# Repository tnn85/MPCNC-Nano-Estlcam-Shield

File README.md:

**<<<BITTE BEACHTEN: Die Platine darf ausdrücklich NUR für die private Verwendung hergestellt werden. Der Weiterverkauf sowohl gewerblich als auch privat (darunter fällt auch der der Verkauf als "gebraucht") ist nicht gestattet. D.h. bitte nicht aus ökonomischen Gründen mehrere Platinen bestellen und dann die übrigen Platinen auf Ebay/Ebay Kleinanzeigen/Amazon/Facebook oder anderen Handelsplattformen öffentlich/halböffentlich anbieten! Beachtet die Lizenzbedingungen am Ende dises Dokuments. Danke für dein/euer Verständnis.>>>**  

Falls Interesse an der Platine besteht und ihr diese nicht selbst fertigen (ätzen/fräsen) wollt oder könnt, bietet der Moderator der FB-Gruppe "Uncle Phil's Werkstatt" die Bausätze an. Ich habe **nur** ihm gestattet, die Platine anzubieten. Andere Bezugsquellen sind von mir nicht genehmigt.

# MPCNC-Nano-Estlcam-Shield
English: A CNC shield for the MPCNC in conjunction with Estlcam  
Deutsch: Ein CNC Shield für die MPCNC in Verbindung mit Estlcam

# Konzept:  
Das MPCNC Nano Esltcam Shield stellt eine CNC Steuerungssplatine für die MPCNC bereit, die Einsteigern eine kostengünstige, auf die CNC-Maschine (MPCNC) und Software (Estlcam) zugeschnittene Steuerung als Schnittstellenlösung zwischen Maschine und Estlcam anbietet.  Die Steuerung bietet mehr Funktionalität als vergleichbare Steuerungen (z. B. das bekannte GRBL 0.8 "CNC Shield V3"), auf die Schrittmotortreibermodule (A4988, DRV8825, etc) gesteckt werden können und stellt zusätzlich eine Erweiterungsmöglichkeit für genauere, leistungsähigere Schrittmotortreiber bereit.

# Name:

 ***"MPCNC Nano Estlcam Shield"***  
 * __"MPCNC"__: Richtet sich vorrangig (aber nicht nur) an Einsteiger in Thema CNC, die mit der MPCNC  anfangen wollen und somit direkt die Kompatibiliät erkennen  
 * __"Nano"__: Auf Arduino Nano basierend  
 * __"Estlcam"__: Ist für die Verwendung mit Estlcam als Steuerungs- und CAM-Software zugeschnitten  
 * __"Shield"__: Soll ausdrücken, dass es, wie bei der Terminologie von Arduino üblich, als Zusatzmodul/"Piggyback" zum Arduino fungieren soll.
 
# Technische Anforderungen:

* Unterstützt Estlcam Version 11 (GRBL oder andere Firmware kann nach entsprechender Konfiguration auch mit der Platine verwendet werden)
* Arduino Nano Support (Original oder Klon)
* Zweilagige Platine
* Nur THT-Bauteile (kein SMD-Löten erforderlich)
* Schraubklemmen oder Stiftleisten für Anschluss externer Komponenten
* Betrieb mit 12-36V
* Konfiguration über Jumper
* Verpolungsschutz Versorgungsanschluss 
* Steckplätze für Pololu Schrittmotortreibermodule DRV8825 + A4988. TMC21x0 sollte auch funktionieren, wurde noch nicht getestet. 
* Mikrostepping über Jumper für Aufstecktreiber einstellbar
* Serienschaltung von zwei Schrittmotoren für X- und Y-Achsen. Einzelner Motor über Jumper auch im Einzelbetrieb möglich.
* Anschlussmöglichkeit von externen Treibern für alle 3 Achsen (DIR, STEP/PUL, GND). Es können auch Servomotoren damit angesteuert werden.
* Lüfteranschluss 12V 
* 7(8) galvanisch getrennte Eingänge (für Eingang 6 muss die Diode auf dem Arduino entfernt werden)
* Ausreichend Eingänge für Endstops/Programmsteuerung/Werkzeuglängensensor/Tastplatte. Eingänge beliebig konfigurierbar.
* 2 Ausgänge für Relais/SSR/etc mit 5V/12V/Open Collector. Ausgänge können über Estlcam angesteuert werden.
* Signalisierrung der Eingänge/Ausgänge über LEDs möglich (für Ausgänge schon vorhanden, bei Eingängen in Reihe schaltbar) 
* Spindel ON/OFF (galvanisch getrennt) +  Drehzahl (PWM / 0-5V / 0-10V) Ausgänge
* 2 analoge Eingänge Drehzahl + Vorschubanpassung
* optional erweiterbar durch ATTiny µC (greift Drehzahlsignal ab) 
* Testpunkte für Fehlersuche

# Optionale Anforderungen:

* Erweiterung um Handradsteuerung (vorraussichtlich nicht möglich, da Estlcam-seitig unterbunden)
* Drehzahlsteuerung von Spindeln/Fräsmotoren ohne FU über µC ATTiny
* Temperaturabhängige Lüfterreglung über PWM mit Temperaturalarm
* Absaugautomatik mit Nachlaufverzögerung 
* Auto Square
* Sicherung für Treiber
* Unterstützung für Trinamic SilentStepStick TMC2100/2130/2208/5160 (Konfiguration über Tristate-Jumper, Seriell, SPI) 
* Anschlussmöglichkeit für Bluetoothmodul (Übertragung von Estlcam über virtuelle serielle Schnittstelle)

# Ordnerstruktur:

* KiCad-Projektdatei
* Schematic (*.sch)
* PCB Layout (*.kicad_pcb)
* Netzliste (*.net)
* Firmware (Ordner für Firmware für Mikrocontroller)
* Enclosure (Ordner für Gehäuse-CAD-Dateien, STL-Dateien, Stecker)
* Docs (Ordner für Anleitung, Berechnungen, Verkabelungsbeispiele, Technisches Datenblatt, etc)
* Parts (Ordner für Datenblätter, Bill of Materials, Lieferanten, etc)
* Libraries (Ordner für projektspezifische Bauteilsymbole und Footprints)
* Readme 
* License

# Lizenz:
* Creative Commons CC-BY-SA-NC 4.0 License
* Created and Copyright by T.Nenz - E-Mail: MPCNCShield(at)outlook.de

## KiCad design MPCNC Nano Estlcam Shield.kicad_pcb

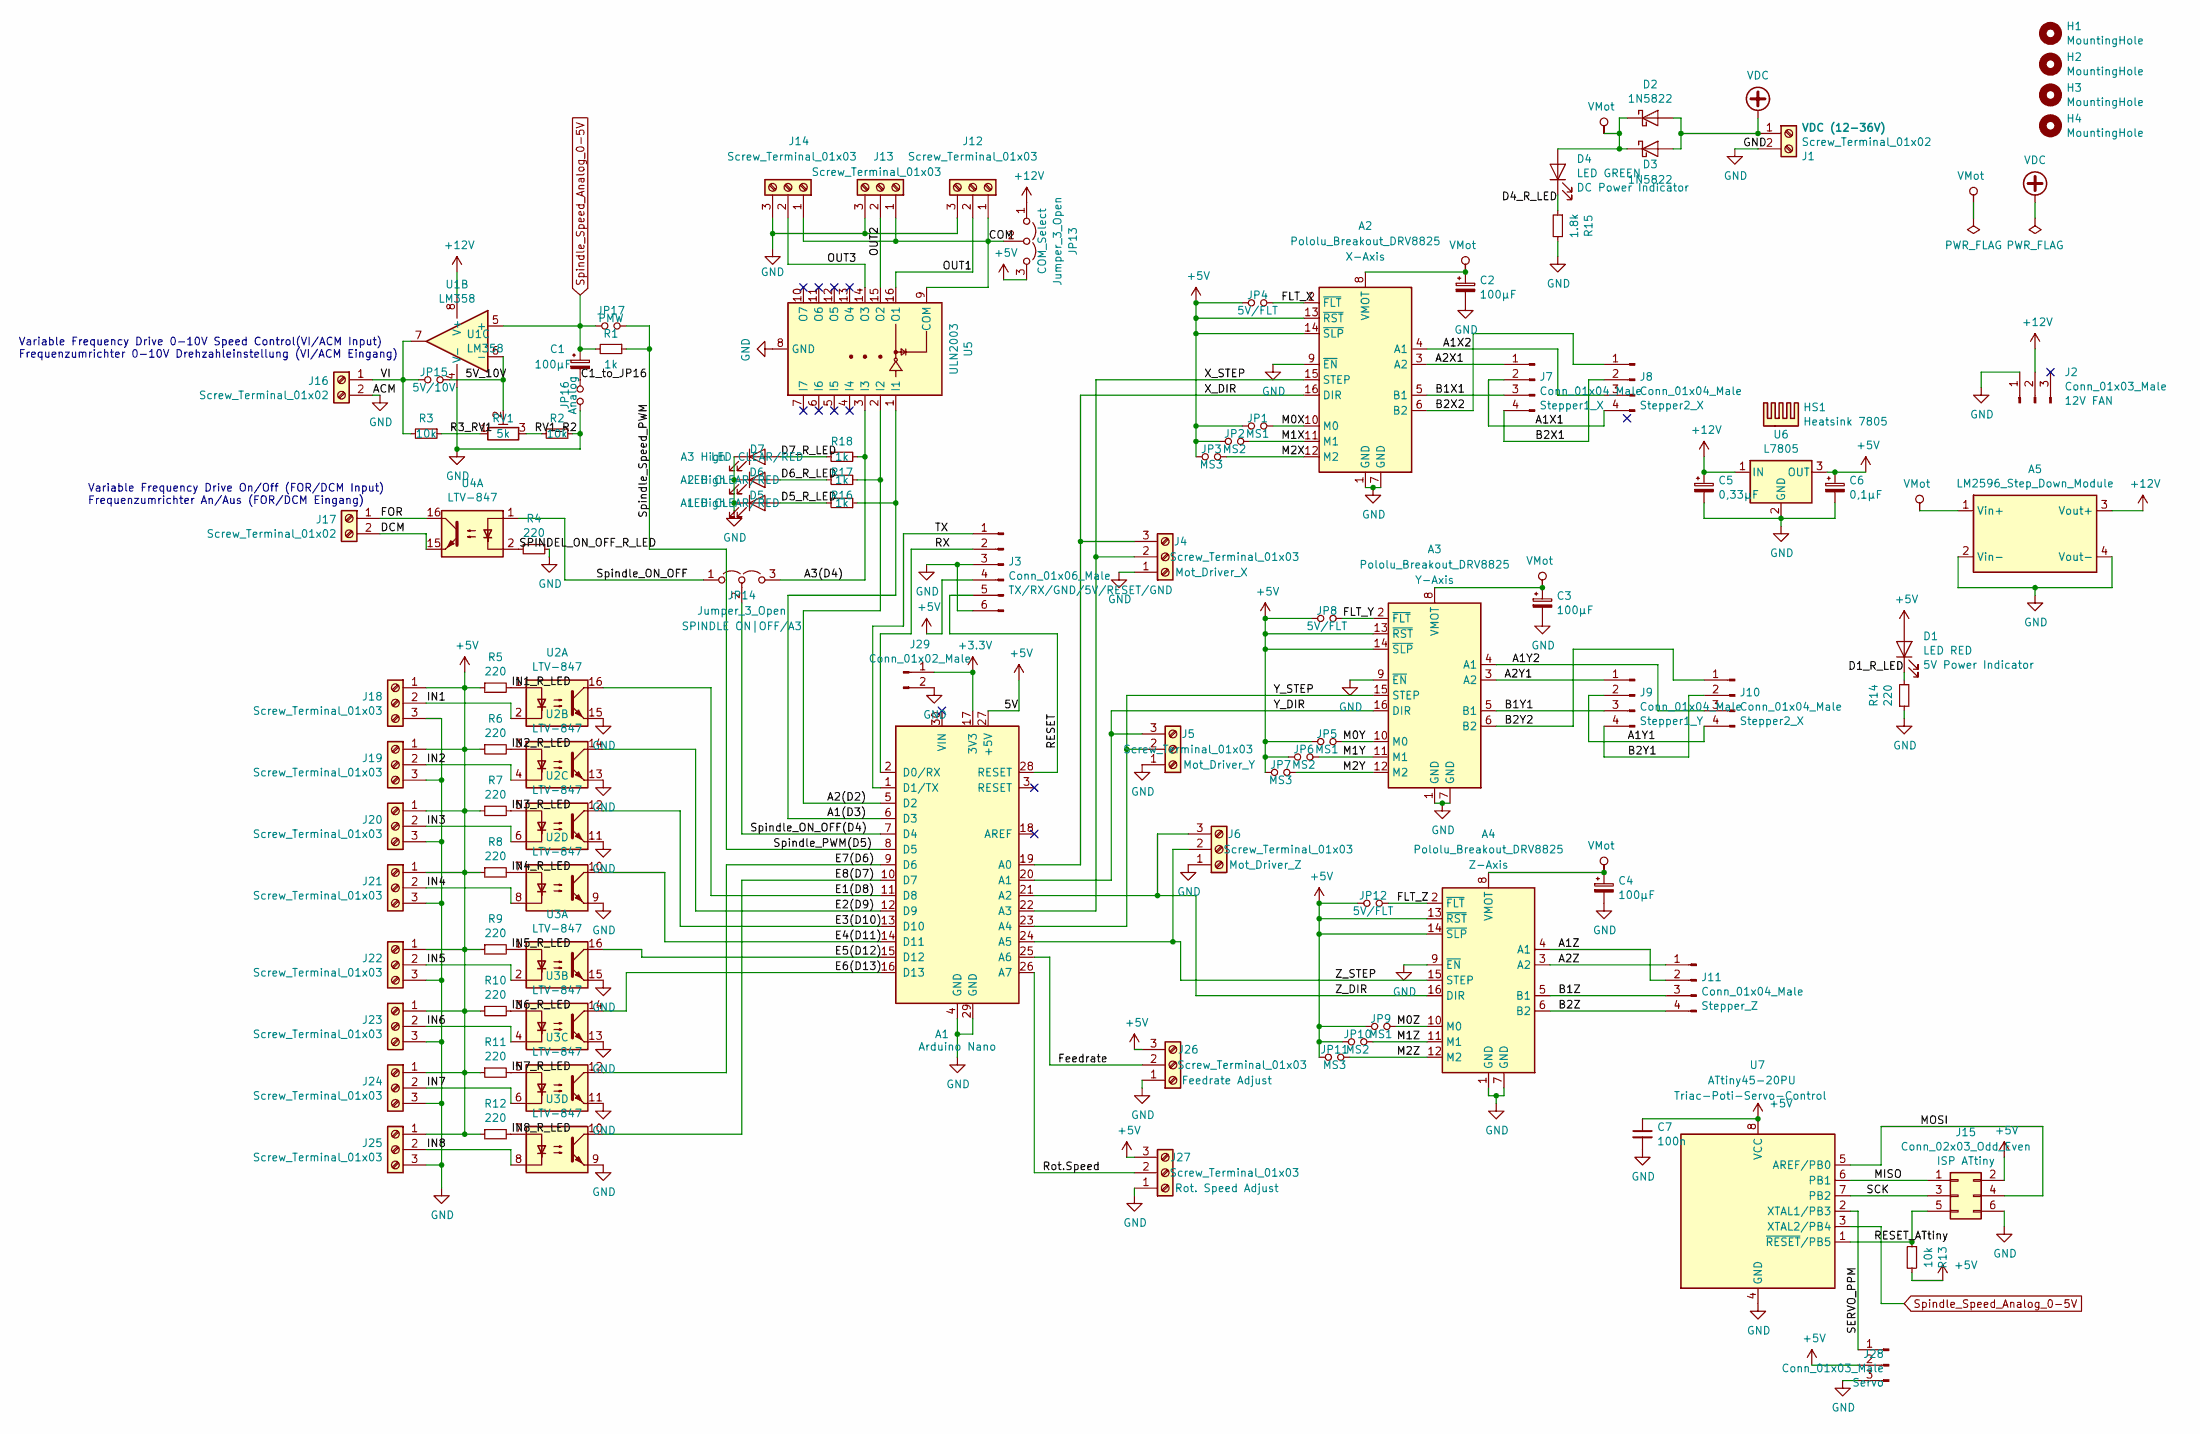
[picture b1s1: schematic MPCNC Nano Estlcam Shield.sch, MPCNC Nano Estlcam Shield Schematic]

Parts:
A1: Arduino Nano; Arduino_Nano
A2, A3, A4: Pololu_Breakout_DRV8825; Pololu_Breakout-16_15.2x20.3mm
A5: LM2596_Step_Down_Module; LM2596_Step_Down_Module-21.3x43.6mm
C1, C2, C3, C4: 100µF; CP_Radial_D8.0mm_P3.50mm
C5: 0,33µF; CP_Radial_D5.0mm_P2.00mm
C6: 0,1µF; CP_Radial_D5.0mm_P2.00mm
C7: 100n; C_Disc_D3.0mm_W1.6mm_P2.50mm
D1: LED RED; LED_D5.0mm_Red
D2, D3: 1N5822; D_DO-201AD_P15.24mm_Horizontal
D4: LED GREEN; LED_D5.0mm_Green
D5, D6, D7: LED CLEAR/RED; LED_D3.0mm_Clear
H1, H2, H3, H4: MountingHole; MountingHole_4.3mm_M4_DIN965_Pad
HS1: Heatsink 7805; Heatsink_China_TO220_(22x)15x10mm_1xDrill1.5mm
J1, J16, J17: Screw_Terminal_01x02; TerminalBlock_RND_205-00012_1x02_P5.00mm_Horizontal
J2: Conn_01x03_Male; Molex_KK-254_AE-6410-03A_1x03_P2.54mm_Vertical
J3: Conn_01x06_Male; PinHeader_1x06_P2.54mm_Vertical
J4, J5, J6, J12, J13, J14, J18, J19, J20, J21, J22, J23, J24, J25, J26, J27: Screw_Terminal_01x03; TerminalBlock_RND_205-00013_1x03_P5.00mm_Horizontal
J7, J8, J9, J10, J11: Conn_01x04_Male; PinHeader_1x04_P2.54mm_Vertical
J15: Conn_02x03_Odd_Even; PinHeader_2x03_P2.54mm_Vertical
J28: Conn_01x03_Male; PinHeader_1x03_P2.54mm_Vertical
J29: Conn_01x02_Male; PinHeader_1x02_P2.54mm_Vertical
JP1, JP2, JP3, JP4, JP5, JP6, JP7, JP8, JP9, JP10, JP11, JP12, JP15, JP16, JP17: Jumper_NO_Small; PinHeader_1x02_P2.54mm_Vertical
JP13, JP14: Jumper_3_Open; PinHeader_1x03_P2.54mm_Vertical
R1, R16, R17, R18: 1k; R_Axial_DIN0207_L6.3mm_D2.5mm_P7.62mm_Horizontal
R2, R3, R13: 10k; R_Axial_DIN0207_L6.3mm_D2.5mm_P7.62mm_Horizontal
R4, R5, R6, R7, R8, R9, R10, R11, R12, R14: 220; R_Axial_DIN0207_L6.3mm_D2.5mm_P7.62mm_Horizontal
R15: 1.8k; R_Axial_DIN0207_L6.3mm_D2.5mm_P7.62mm_Horizontal
RV1: 5k; Potentiometer_Bourns_3296W_Vertical
U1: LM358; DIP-8_W7.62mm
U2, U3, U4: LTV-847; DIP-16_W7.62mm
U5: ULN2003; DIP-16_W7.62mm
U6: L7805; TO-220-3_Vertical
U7: ATtiny45-20PU; DIP-8_W7.62mm

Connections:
+3V3: A1.17 (3V3), J29.1
+5V: A1.27 (+5V), A2.13 (~RST), A2.14 (~SLP), A3.13 (~RST), A3.14 (~SLP), A4.13 (~RST), A4.14 (~SLP), C6.1, C7.1, D1.2 (A), J3.4, J15.2, J18.1, J19.1, J20.1, J21.1, J22.1, J23.1, J24.1, J25.1, J26.3, J27.3, J28.2, JP1.1, JP2.1, JP3.1, JP4.1, JP5.1, JP6.1, JP7.1, JP8.1, JP9.1, JP10.1, JP11.1, JP12.1, JP13.3 (B), R5.1, R6.1, R7.1, R8.1, R9.1, R10.1, R11.1, R12.1, R13.2, U6.3 (OUT), U7.8 (VCC)
+12V: A5.3 (Vout+), C5.1, J2.2, JP13.1 (A), U1.8 (V+), U6.1 (IN)
/5V_10V: JP15.2, RV1.2, U1.6 (-)
/A1(D3): A1.6 (D3), R16.1, U5.1 (I1)
/A1X1: J7.2, J8.4
/A1X2: A2.4 (A1), J8.3
/A1Y1: J9.2, J10.4
/A1Y2: A3.4 (A1), J10.3
/A1Z: A4.4 (A1), J11.2
/A2(D2): A1.5 (D2), R17.1, U5.2 (I2)
/A2X1: A2.3 (A2), J7.1
/A2Y1: A3.3 (A2), J9.1
/A2Z: A4.3 (A2), J11.1
/A3(D4): JP14.3 (B), R18.2, U5.3 (I3)
/B1X1: A2.5 (B1), J7.3
/B1Y1: A3.5 (B1), J9.3
/B1Z: A4.5 (B1), J11.3
/B2X1: J7.4, J8.2
/B2X2: A2.6 (B2), J8.1
/B2Y1: J9.4, J10.2
/B2Y2: A3.6 (B2), J10.1
/B2Z: A4.6 (B2), J11.4
/C1_to_JP16: C1.2, JP16.1
/COM: J12.1, J13.1, J14.1, JP13.2 (C), U5.9 (COM)
/D1_R_LED: D1.1 (K), R14.2
/D4_R_LED: D4.1 (K), R15.1
/D5_R_LED: D5.2 (A), R16.2
/D6_R_LED: D6.2 (A), R17.2
/D7_R_LED: D7.2 (A), R18.1
/DCM: J17.2, U4.15
/E1(D8): A1.11 (D8), U2.16
/E2(D9): A1.12 (D9), U2.14
/E3(D10): A1.13 (D10), U2.12
/E4(D11): A1.14 (D11), U2.10
/E5(D12): A1.15 (D12), U3.16
/E6(D13): A1.16 (D13), U3.14
/E7(D6): A1.9 (D6), U3.12
/E8(D7): A1.10 (D7), U3.10
/FLT_X: A2.2 (~FLT), JP4.2
/FLT_Y: A3.2 (~FLT), JP8.2
/FLT_Z: A4.2 (~FLT), JP12.2
/FOR: J17.1, U4.16
/Feedrate: A1.25 (A6), J26.2
/IN1: J18.2, U2.2
/IN1_R_LED: R5.2, U2.1
/IN2: J19.2, U2.4
/IN2_R_LED: R6.2, U2.3
/IN3: J20.2, U2.6
/IN3_R_LED: R7.2, U2.5
/IN4: J21.2, U2.8
/IN4_R_LED: R8.2, U2.7
/IN5: J22.2, U3.2
/IN5_R_LED: R9.2, U3.1
/IN6: J23.2, U3.4
/IN6_R_LED: R10.2, U3.3
/IN7: J24.2, U3.6
/IN7_R_LED: R11.2, U3.5
/IN8: J25.2, U3.8
/IN8_R_LED: R12.2, U3.7
/M0X: A2.10 (M0), JP1.2
/M0Y: A3.10 (M0), JP5.2
/M0Z: A4.10 (M0), JP9.2
/M1X: A2.11 (M1), JP2.2
/M1Y: A3.11 (M1), JP6.2
/M1Z: A4.11 (M1), JP10.2
/M2X: A2.12 (M2), JP3.2
/M2Y: A3.12 (M2), JP7.2
/M2Z: A4.12 (M2), JP11.2
/MISO: J15.1, U7.6 (PB1)
/MOSI: J15.4, U7.5 (AREF/PB0)
/OUT1: J12.2, U5.16 (O1)
/OUT2: J13.2, U5.15 (O2)
/OUT3: J14.2, U5.14 (O3)
/R3_RV1: R3.1, RV1.1
/RESET: A1.28 (RESET), J3.5
/RESET_ATtiny: J15.5, R13.1, U7.1 (~RESET~/PB5)
/RV1_R2: R2.2, RV1.3
/RX: A1.2 (D0/RX), J3.2
/Rot.Speed: A1.26 (A7), J27.2
/SCK: J15.3, U7.7 (PB2)
/SERVO_PPM: J28.1, U7.2 (XTAL1/PB3)
/SPINDEL_ON_OFF_R_LED: R4.2, U4.2
/Spindle_ON_OFF: JP14.1 (A), U4.1
/Spindle_ON_OFF(D4): A1.7 (D4), JP14.2 (C)
/Spindle_PWM(D5): A1.8 (D5), JP17.1, R1.1
/TX: A1.1 (D1/TX), J3.1
/VI: J16.1, JP15.1, R3.2, U1.7
/X_DIR: A1.19 (A0), A2.16 (DIR), J4.3
/X_STEP: A1.22 (A3), A2.15 (STEP), J4.2
/Y_DIR: A1.20 (A1), A3.16 (DIR), J5.3
/Y_STEP: A1.23 (A4), A3.15 (STEP), J5.2
/Z_DIR: A1.21 (A2), A4.16 (DIR), J6.3
/Z_STEP: A1.24 (A5), A4.15 (STEP), J6.2
GND: A1.4 (GND), A1.29 (GND), A2.1 (GND), A2.7 (GND), A2.9 (~EN), A3.1 (GND), A3.7 (GND), A3.9 (~EN), A4.1 (GND), A4.7 (GND), A4.9 (~EN), A5.2 (Vin-), A5.4 (Vout-), C2.2, C3.2, C4.2, C5.2, C6.2, C7.2, D5.1 (K), D6.1 (K), D7.1 (K), J1.2, J2.1, J3.3, J3.6, J4.1, J5.1, J6.1, J12.3, J13.3, J14.3, J15.6, J16.2, J18.3, J19.3, J20.3, J21.3, J22.3, J23.3, J24.3, J25.3, J26.1, J27.1, J28.3, J29.2, JP16.2, R2.1, R4.1, R14.1, R15.2, U1.4 (V-), U2.9, U2.11, U2.13, U2.15, U3.9, U3.11, U3.13, U3.15, U5.8 (GND), U6.2 (GND), U7.4 (GND)
Spindle_Speed_Analog_0-5V: C1.1, JP17.2, R1.2, U1.5 (+), U7.3 (XTAL2/PB4)
VDC: D2.2 (A), D3.2 (A), J1.1
VMot: A2.8 (VMOT), A3.8 (VMOT), A4.8 (VMOT), A5.1 (Vin+), C2.1, C3.1, C4.1, D2.1 (K), D3.1 (K), D4.2 (A)

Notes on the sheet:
Variable Frequency Drive On/Off (FOR/DCM Input) Frequenzumrichter An/Aus (FOR/DCM Eingang)
Variable Frequency Drive 0-10V Speed Control(VI/ACM Input) Frequenzumrichter 0-10V Drehzahleinstellung (VI/ACM Eingang)

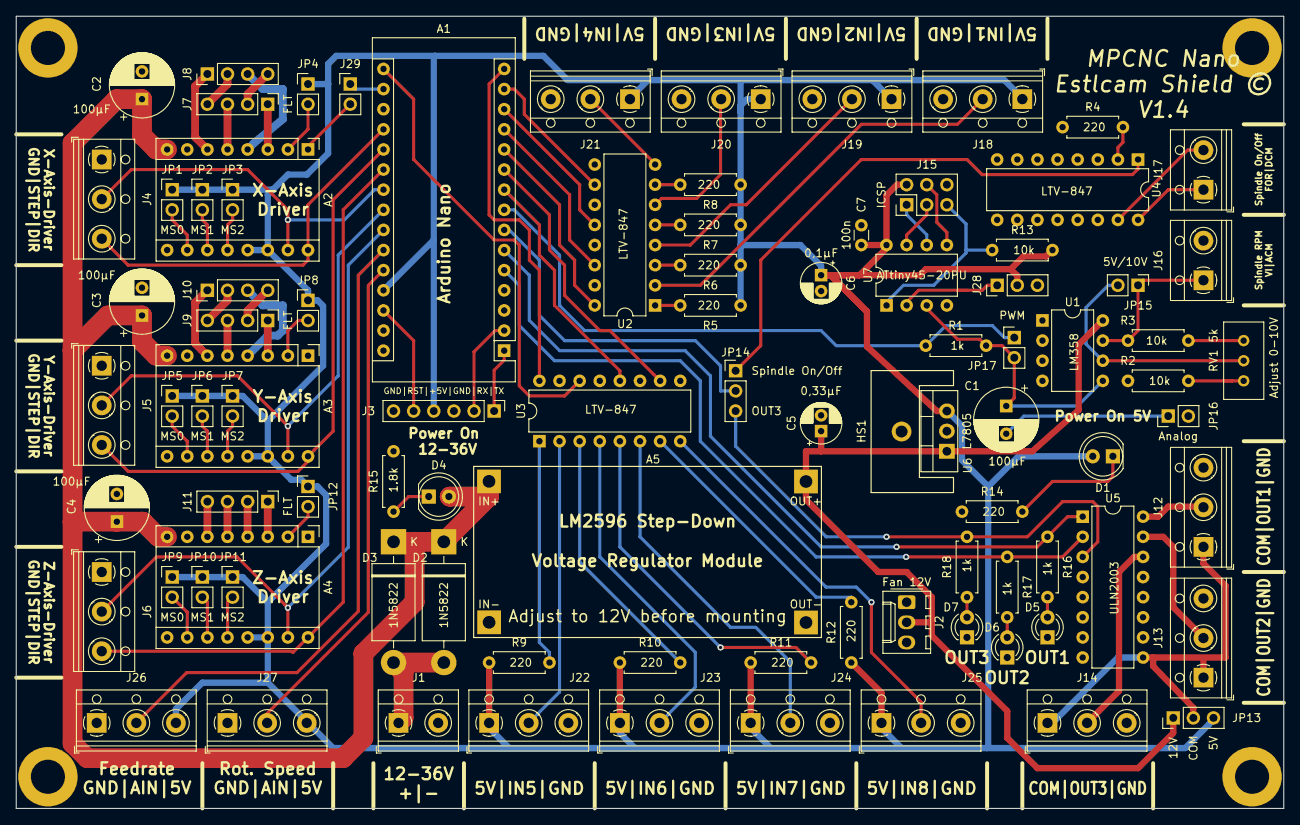
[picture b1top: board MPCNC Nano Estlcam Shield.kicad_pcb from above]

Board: 2 copper layers, 160.0 x 100.0 mm, 96 parts (0 on the bottom side), 98 nets.

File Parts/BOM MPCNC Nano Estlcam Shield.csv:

ID;Bezeichner;Gehäuse;Stückzahl;Bezeichnung;Anbieter und Referenz;;Stückpreis;Gesamtpreis;Optional;Erklärung;;;
26;A1;Arduino_Nano;1;Arduino_Nano_v3.x;;https://www.reichelt.de/arduino-nano-v3-3-atmega-328-mini-us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; 1,65  ; 1,65  ;x;;;;
6;C7;C_Disc_D3.0mm_W1.6mm_P2.50mm;1;100n;;https://www.reichelt.de/vielschicht-keramikkondensator-100n-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; 0,05  ; 0,05  ;;;;;
23;C3,C2,C1,C4;CP_Radial_D8.0mm_P3.50mm;4;100µF;;https://www.reichelt.de/elko-radial-100-uf-50-v-105-c-low-es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; 0,21  ; 0,84  ;;;;;
25;C5, C6;CP_Radial_D8.0mm_P3.50mm;2;1µF;;"https://www.reichelt.de/Elkos-radial-85-C/2/index.html?ACTIO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;SID=95XH8Os6wQAT4AAAsVaKsfa9052d4429531c64a0053c122c792f8"; 0,04  ; 0,08  ;;;;;
1;D3,D2;D_DO-201AD_P15.24mm_Horizontal;2;1N5822;;https://www.reichelt.de/schottkydiode-40-v-3-a-do-201ad-rnd-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; 0,12  ; 0,24  ;;;;;
16;U5;DIP-16_W7.62mm;1;ULN2003AN;;https://www.reichelt.de/darlington-arrays-konstantstromregle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; 0,55  ; 0,55  ;;;;;
28;U3,U4,U2;DIP-16_W7.62mm;3;LTV-847;;https://www.reichelt.de/optokoppler-ltv-847-p76176.html?&trs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; 0,52  ; 1,56  ;;;;;
11;U1;DIP-8_W7.62mm;1;LM358;;https://www.reichelt.de/operationsverstaerker-2-fach-dip-8-l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; 0,24  ; 0,24  ;;;;;
12;U7;DIP-8_W7.62mm_LongPads;1;ATtiny45-20PU;;https://www.reichelt.de/mcu-attiny-avr-risc-4-kb-20-mhz-pdip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; 0,90  ; 0,90  ;x;Nur wenn Servoausgang benötigt;;;
15;HS1;Heatsink_China_TO220_(22x)15x10mm_1xDrill1.5mm;1;Heatsink 7805;;https://www.aliexpress.com/item/10pcs-Aluminium-TO-220-Heats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; 0,54  ; 0,54  ;;;;;
2;D1;LED_D5.0mm;1;LED;;https://www.reichelt.de/led-5-mm-bedrahtet-rot-800-mcd-15-rn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; 0,04  ; 0,04  ;;;;;
5;A5;LM2596_Step_Down_Module-4_21.2x40.3mm;1;LM2596_Step_Down_Module;;https://www.aliexpress.com/item/3A-Voltage-regulator-lm2596-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; 0,67  ; 0,67  ;x;Nur bei Versorgung >12V;;;
19;J2;Molex_KK-254_AE-6410-03A_1x03_P2.54mm_Vertical;1;Conn_01x03_Male;;https://www.reichelt.de/molex-stiftleiste-kk-1x3-polig-steck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; 0,26  ; 0,26  ;x;Nur bei Anschluss von PC Lüfter, Stiftleiste geht auch;;;
4;J29;PinHeader_1x02_P2.54mm_Vertical;16;Conn_01x02_Male;;https://www.reichelt.de/rnd-stiftleiste-2-pol-rm-2-54-mm-rnd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; 0,07  ; 1,12  ;;;;;
17;JP2,JP16,JP17,JP3,JP8,JP10,JP5,JP15,JP11,JP7,JP6,JP9,JP12,JP4,JP1;PinHeader_1x02_P2.54mm_Vertical;15;Jumper_NO_Small;;https://www.reichelt.de/kurzschlussbruecke-gruen-rm-2-54-ver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; 0,01  ; 0,15  ;;Zusätzlich Stifleisten 1x02;;;
8;J28;PinHeader_1x03_P2.54mm_Vertical;3;Conn_01x03_Male;;https://www.reichelt.de/rnd-stiftleiste-3-pol-rm-2-54-mm-rnd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; 0,02  ; 0,06  ;;;;;
18;JP14,JP13;PinHeader_1x03_P2.54mm_Vertical;2;Jumper_NC_Dual;;https://www.reichelt.de/kurzschlussbruecke-gruen-rm-2-54-ver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; 0,01  ; 0,02  ;;Zusätzlich Stifleisten 1x03;;;
20;J8,J7,J11,J10,J9;PinHeader_1x04_P2.54mm_Vertical;5;Conn_01x04_Male;;https://www.reichelt.de/rnd-stiftleiste-4-pol-rm-2-54-mm-rnd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; 0,02  ; 0,10  ;;;;;
13;J3;PinHeader_1x06_P2.54mm_Vertical;1;Conn_01x06_Male;;https://www.reichelt.de/rnd-stiftleiste-6-pol-rm-2-54-mm-rnd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; 0,05  ; 0,05  ;x;Nur wenn Servoausgang benötigt;;;
9;J15;PinHeader_2x03_P2.54mm_Vertical;1;Conn_02x03_Odd_Even;;https://www.reichelt.de/rnd-stiftleiste-6-pol-rm-2-54-mm-rnd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; 0,30  ; 0,30  ;;;;;
24;A2,A3,A4;PinSocket_1x15_P2.54mm_Vertical;2;Conn_01x15_Female;;https://www.reichelt.de/20pol-buchsenleiste-gerade-rm-2-54-h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; 0,27  ; 0,54  ;;Für Arduino. Auf Länge kürzen mit heißem Cuttermesser;;;
26;A1;PinSocket_1x08_P2.54mm_Vertical;6;Conn_01x08_Female;;https://www.reichelt.de/rnd-buchsenleiste-8-pol-rm-2-54-mm-r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; 0,15  ; 0,90  ;;Für DRV8825 Treiber;;;
24;A2,A4,A3;Pololu_Breakout-16_15.2x20.3mm;3;Pololu_Breakout_DRV8825;;https://www.aliexpress.com/item/3D-Printer-Parts-StepStick-A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; 0,95  ; 2,85  ;x;;;;
7;RV1;Potentiometer_Bourns_3296Y_Vertical;1;5k;;https://www.reichelt.de/praezisionspotentiometer-25-gaenge-s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; 0,23  ; 0,23  ;;;;; 1,89  
3;R14,R8,R12,R11,R10,R9,R7,R6,R5,R4;R_Axial_DIN0207_L6.3mm_D2.5mm_P7.62mm_Horizontal;10;220 Ohm;;https://www.reichelt.de/widerstand-kohleschicht-220-ohm-0207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; 0,08  ; 0,80  ;;;;;
10;R13,R3,R2;R_Axial_DIN0207_L6.3mm_D2.5mm_P7.62mm_Horizontal;3;10k;;https://www.reichelt.de/widerstand-kohleschicht-10-kohm-0207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; 0,08  ; 0,24  ;;;;;
29;R1;R_Axial_DIN0207_L6.3mm_D2.5mm_P7.62mm_Horizontal;1;1k;;https://www.reichelt.de/widerstand-kohleschicht-1-0-kohm-020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; 0,08  ; 0,08  ;;;;;
21;J16,J17,J1;TerminalBlock_Phoenix_MKDS-1,5-2-5.08_1x02_P5.08mm_Horizontal;3;Screw_Terminal_01x02;;https://www.reichelt.de/loetbare-schraubklemme-2-pol-rm-5-08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; 0,26  ; 0,78  ;;Chinapreis;0,16 ;https://de.aliexpress.com/item/5-st-cke-PCB-Schraube-Termina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;
14;J22,J25,J12,J27,J26,J24,J23,J21,J6,J5,J4,J14,J13,J20,J19,J18;TerminalBlock_Phoenix_MKDS-1,5-3-5.08_1x03_P5.08mm_Horizontal;16;Screw_Terminal_01x03;;https://www.reichelt.de/loetbare-schraubklemme-3-pol-rm-5-08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; 0,35  ; 5,60  ;;Chinapreis;2,95 ;https://de.aliexpress.com/item/5-st-cke-PCB-Schraube-Termina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;
22;U6;TO-220-3_Vertical;1;L7805;;https://www.reichelt.de/spannungsregler-fest-5-v-to-220-mc-7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; 0,29  ; 0,29  ;;;;;
;;;;;;;; 15,35  ;;;;;

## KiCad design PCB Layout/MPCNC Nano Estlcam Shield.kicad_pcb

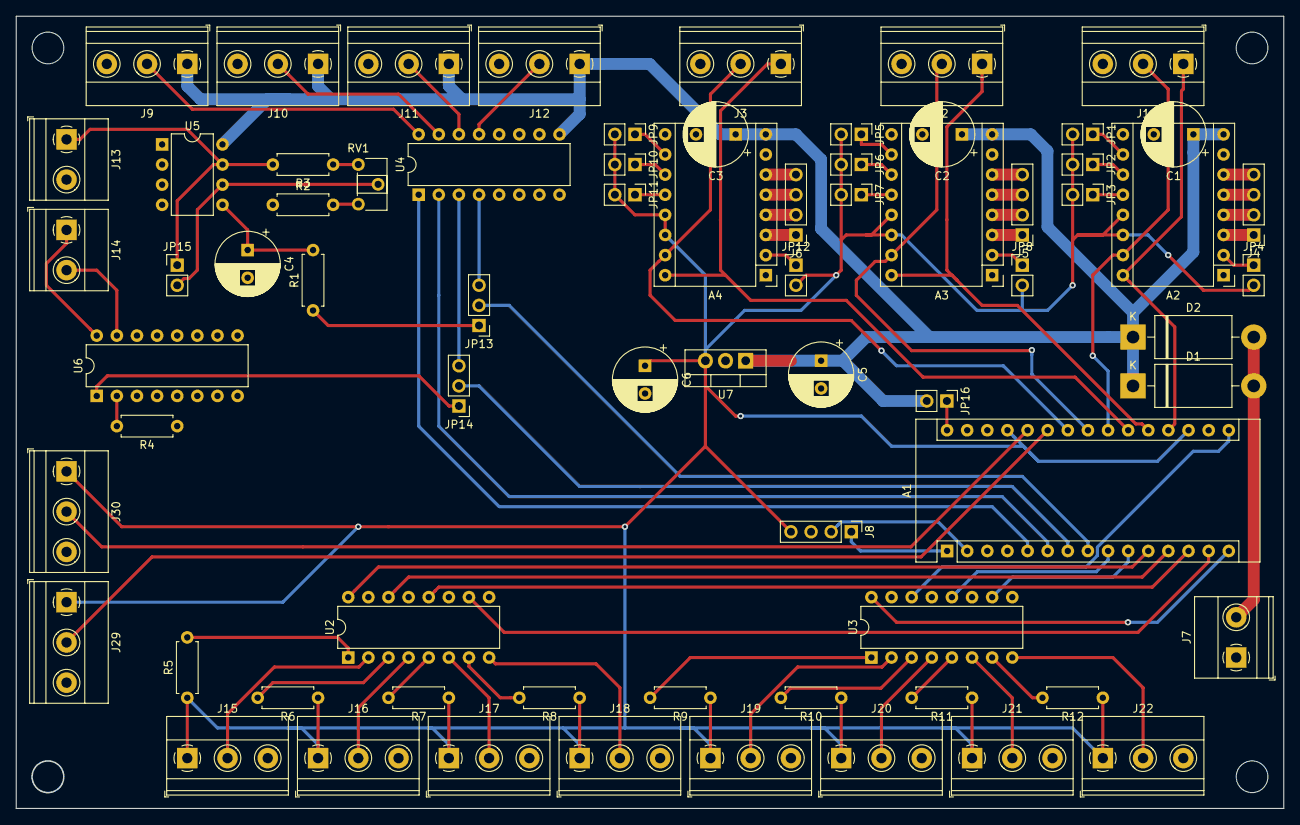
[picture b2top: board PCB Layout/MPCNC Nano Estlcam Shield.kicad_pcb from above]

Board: 2 copper layers, 159.9 x 99.9 mm, 71 parts (0 on the bottom side), 83 nets.

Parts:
A1: Arduino_Nano_v3.x; Arduino_Nano
A2: X_Axis_Pololu_Breakout_DRV8825; Pololu_Breakout-16_15.2x20.3mm
A3: Y_Axis_Pololu_Breakout_DRV8825; Pololu_Breakout-16_15.2x20.3mm
A4: Z_Axis_Pololu_Breakout_DRV8825; Pololu_Breakout-16_15.2x20.3mm
C1, C2, C3: 100µF; CP_Radial_D8.0mm_P5.00mm
C4: 100µF; CP_Radial_D8.0mm_P3.50mm
C5: 1µF; CP_Radial_D8.0mm_P3.50mm
C6: 0.1µF; CP_Radial_D8.0mm_P3.50mm
D1, D2: 1N5822; D_DO-201AD_P15.24mm_Horizontal
J1: Mot_Driver_X; TerminalBlock_Phoenix_MKDS-1,5-3-5.08_1x03_P5.08mm_Horizont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
J2: Mot_Driver_Y; TerminalBlock_Phoenix_MKDS-1,5-3-5.08_1x03_P5.08mm_Horizont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
J3: Mot_Driver_Z; TerminalBlock_Phoenix_MKDS-1,5-3-5.08_1x03_P5.08mm_Horizont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
J4: Stepper_X; PinHeader_1x04_P2.54mm_Vertical
J5: Stepper_Y; PinHeader_1x04_P2.54mm_Vertical
J6: Stepper_Z; PinHeader_1x04_P2.54mm_Vertical
J7: 9-20V; TerminalBlock_Phoenix_MKDS-1,5-2-5.08_1x02_P5.08mm_Horizont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
J8: Serial Tx/Rx; PinHeader_1x04_P2.54mm_Vertical
J9: A2; TerminalBlock_Phoenix_MKDS-1,5-3-5.08_1x03_P5.08mm_Horizont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
J10: A1; TerminalBlock_Phoenix_MKDS-1,5-3-5.08_1x03_P5.08mm_Horizont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
J11: A4; TerminalBlock_Phoenix_MKDS-1,5-3-5.08_1x03_P5.08mm_Horizont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
J12: A3; TerminalBlock_Phoenix_MKDS-1,5-3-5.08_1x03_P5.08mm_Horizont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
J13: VI/ACM; TerminalBlock_Phoenix_MKDS-1,5-2-5.08_1x02_P5.08mm_Horizont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
J14: FOR/DCM; TerminalBlock_Phoenix_MKDS-1,5-2-5.08_1x02_P5.08mm_Horizont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
J15: E1; TerminalBlock_Phoenix_MKDS-1,5-3-5.08_1x03_P5.08mm_Horizont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
J16: E2; TerminalBlock_Phoenix_MKDS-1,5-3-5.08_1x03_P5.08mm_Horizont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
J17: E3; TerminalBlock_Phoenix_MKDS-1,5-3-5.08_1x03_P5.08mm_Horizont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
J18: E4; TerminalBlock_Phoenix_MKDS-1,5-3-5.08_1x03_P5.08mm_Horizont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
J19: E5; TerminalBlock_Phoenix_MKDS-1,5-3-5.08_1x03_P5.08mm_Horizont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
J20: E6; TerminalBlock_Phoenix_MKDS-1,5-3-5.08_1x03_P5.08mm_Horizont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
J21: E7; TerminalBlock_Phoenix_MKDS-1,5-3-5.08_1x03_P5.08mm_Horizont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
J22: E8; TerminalBlock_Phoenix_MKDS-1,5-3-5.08_1x03_P5.08mm_Horizont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
J29: Feedrate; TerminalBlock_Phoenix_MKDS-1,5-3-5.08_1x03_P5.08mm_Horizont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
J30: Rot. Speed; TerminalBlock_Phoenix_MKDS-1,5-3-5.08_1x03_P5.08mm_Horizont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
JP1, JP5, JP9: MS1; PinHeader_1x02_P2.54mm_Vertical
JP2, JP6, JP10: MS2; PinHeader_1x02_P2.54mm_Vertical
JP3, JP7, JP11: MS3; PinHeader_1x02_P2.54mm_Vertical
JP4, JP8, JP12: 5V/FLT; PinHeader_1x02_P2.54mm_Vertical
JP13: PWM/A3; PinHeader_1x03_P2.54mm_Vertical
JP14: SPINDLE ON/OFF/A4; PinHeader_1x03_P2.54mm_Vertical
JP15: 5V/10V; PinHeader_1x02_P2.54mm_Vertical
JP16: Ext. Power; PinHeader_1x02_P2.54mm_Vertical
R1: 1k; R_Axial_DIN0207_L6.3mm_D2.5mm_P7.62mm_Horizontal
R2, R3: 10k; R_Axial_DIN0207_L6.3mm_D2.5mm_P7.62mm_Horizontal
R4, R5, R6, R7, R8, R9, R10, R11, R12: 220; R_Axial_DIN0207_L6.3mm_D2.5mm_P7.62mm_Horizontal
RV1: 5k; Potentiometer_ACP_CA6-H2,5_Horizontal
U2, U3, U6: LTV-847; DIP-16_W7.62mm
U4: ULN2003; DIP-16_W7.62mm
U5: LM358; DIP-8_W7.62mm
U7: L7805; TO-220-3_Vertical

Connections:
+5V: A1.18, A1.27, A2.13, A2.14, A3.13, A3.14, A4.13, A4.14, C6.1, J8.4, J15.1, J16.1, J17.1, J18.1, J19.1, J20.1, J21.1, J22.1, J29.1, J30.1, JP1.2, JP2.2, JP3.2, JP4.2, JP5.2, JP6.2, JP7.2, JP8.2, JP9.2, JP10.2, JP11.2, JP12.2, R5.1, R6.1, R7.1, R8.1, R9.1, R10.1, R11.1, R12.1, U7.3
/5V_10V: JP15.2, RV1.2, U5.6
/A1: J10.2, U4.15
/A1(D3): A1.6, U4.2
/A1X: A2.4, J4.2
/A1Y: A3.4, J5.2
/A1Z: A4.4, J6.2
/A2: J9.2, U4.16
/A2(D2): A1.5, U4.1
/A2X: A2.3, J4.1
/A2Y: A3.3, J5.1
/A2Z: A4.3, J6.1
/A3: J12.2, U4.13
/A3(D5): JP13.3, U4.4
/A4: J11.2, U4.14
/A4(D4): JP14.3, U4.3
/B1X: A2.5, J4.3
/B1Y: A3.5, J5.3
/B1Z: A4.5, J6.3
/B2X: A2.6, J4.4
/B2Y: A3.6, J5.4
/B2Z: A4.6, J6.4
/DCM: J14.2, U6.15
/DC_Power: D1.2, D2.2, J7.2
/E1: J15.2, U2.2
/E1(D8): A1.11, U2.16
/E2: J16.2, U2.4
/E2(D9): A1.12, U2.14
/E3: J17.2, U2.6
/E3(D10): A1.13, U2.12
/E4: J18.2, U2.8
/E4(D11): A1.14, U2.10
/E5: J19.2, U3.2
/E5(D12): A1.15, U3.16
/E6: J20.2, U3.4
/E6(D13): A1.16, U3.14
/E7: J21.2, U3.6
/E7(D6): A1.9, U3.12
/E8: J22.2, U3.8
/E8(D7): A1.10, U3.10
/FOR: J14.1, U6.16
/Feedrate: A1.25, J29.2
/PWM: JP13.1, R1.1
/PWM(D5): A1.8, JP13.2
/RX: A1.2, J8.2
/Rot.Speed: A1.26, J30.2
/Spindle_ON_OFF: JP14.1, U6.1
/Spindle_ON_OFF(D4): A1.7, JP14.2
/TX: A1.1, J8.1
/VI: J13.1, JP15.1, R3.2, U5.7
/VIN: A1.30, JP16.1
/X_DIR: A1.19, A2.16, J1.1
/X_STEP: A1.22, A2.15, J1.2
/Y_DIR: A1.20, A3.16, J2.1
/Y_STEP: A1.23, A3.15, J2.2
/Z_DIR: A1.21, A4.16, J3.1
/Z_STEP: A1.24, A4.15, J3.2
GND: A1.4, A1.29, A2.1, A2.7, A2.9, A3.1, A3.7, A3.9, A4.1, A4.7, A4.9, C1.2, C2.2, C3.2, C4.2, C5.2, C6.2, J1.3, J2.3, J3.3, J7.1, J8.3, J9.3, J10.3, J11.3, J12.3, J13.2, J15.3, J16.3, J17.3, J18.3, J19.3, J20.3, J21.3, J22.3, J29.3, J30.3, R2.1, R4.1, U2.9, U2.11, U2.13, U2.15, U3.9, U3.11, U3.13, U3.15, U4.8, U5.4, U7.2
unnamed: A2.2, JP4.1
unnamed: A2.10, JP1.1
unnamed: A2.11, JP2.1
unnamed: A2.12, JP3.1
unnamed: A3.2, JP8.1
unnamed: A3.10, JP5.1
unnamed: A3.11, JP6.1
unnamed: A3.12, JP7.1
unnamed: A4.2, JP12.1
unnamed: A4.10, JP9.1
unnamed: A4.11, JP10.1
unnamed: A4.12, JP11.1
unnamed: C4.1, R1.2, U5.5
unnamed: R2.2, RV1.3
unnamed: R3.1, RV1.1
unnamed: R4.2, U6.2
unnamed: R5.2, U2.1
unnamed: R6.2, U2.3
unnamed: R7.2, U2.5
unnamed: R8.2, U2.7
unnamed: R9.2, U3.1
unnamed: R10.2, U3.3
unnamed: R11.2, U3.5
unnamed: R12.2, U3.7
VDD: A2.8, A3.8, A4.8, C1.1, C2.1, C3.1, C5.1, D1.1, D2.1, J9.1, J10.1, J11.1, J12.1, JP16.2, U4.9, U5.8, U7.1

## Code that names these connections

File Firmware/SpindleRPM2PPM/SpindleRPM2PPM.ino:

/*
 * Spindle RPM-Signal to PPM-Signal conversion (e.g. for controlling RC model motor with ESCs, RC model servos)  
 * 
 * Author: Till Nenz
 * Date: 20.07.2020
 * Version: 0.1
 * 
 * Description:
 * Reads an analog input pin (Signal "Spindle_Speed_Analog_0-5V"), 
 * maps the result to a range from MIN_PPM_PULSE (default 1000µs) to MAX_PPM_PULSE (default 2000µs) and uses
 * the result to set the pulse pause modulated signal (PPM) of an output pin (Signal "Servo_PPM").
 * Debug: If activated, prints the results to the Serial Monitor (however, this causes the servo signal to jitter and should only be used to debug).
 * 
 * Required IC:
 * -ATtiny25/45/85-20PU (Package: PDIP) (tested with ATtiny85) (ATtiny 25 Program space might be too small for future releases)
 * 
 * Required Software:
 * -Arduino IDE 1.8.13 or newer
 * -ATTiny Core by SpenceKonde (https://github.com/SpenceKonde/ATTinyCore/blob/master/Installation.md)
 * 
 * Required chip fuse settings:
 * -ATtiny fuse bytes have to be programmed before flashing this firmware
 * -Low Fuse: 0xE2; High Fuse: 0xDF; Extended Fuse: 0xFF;  (AVRDUDE: -U lfuse:w:0xe2:m -U hfuse:w:0xdf:m -U efuse:w:0xff:m)
 * 
 * The circuit:
 *   - see "MPCNC Nano Estlcam Shield V1.x.pdf" schematic
 *   - connect Servo/ESC to J28 pin header (white cable [servo signal] left pin [facing to the µC/ATtiny], red cable [VCC/5V] middle pin, black cable [GND] right pin)
 *   - UART debug output (Baud: 115200 bit/s) on MOSI pin (Pin 5/PB0/Arduino Pin 0) (see https://github.com/SpenceKonde/ATTinyCore/blob/master/avr/extras/ATtiny_x5.md) connected to the ICSP header
 * 
 * based on:   
 * https://github.com/SpenceKonde/ATTinyCore/blob/master/avr/libraries/Servo_ATTinyCore/examples/Knob/Knob.ino
 * 
 */

#include <Servo_ATTinyCore.h>

//#define DEBUG_SERIAL

// Pin definitions
#define ANALOG_SPINDLE_RPM_IN_PIN  A2  // Analog input pin that the Arduino Nano spindle RPM signal is attached to
#define PPM_SPINDLE_RPM_OUT_PIN  3 //  // Digital output pin that the motor ESC / servo is attached to

// ESC/Servo PPM pulse length [µs]
#define MIN_PPM_PULSE 1000
#define MAX_PPM_PULSE 2000

int analogSpindleRPMValue = 0;        // value read from the input spindle RPM signal
int ppmSpindleRPMValue = 0;           // value pulse length [µ output to the PPM 

Servo servo_esc;  // create servo object to control an esc or servo

void setup() {
#ifdef DEBUG_SERIAL
  // initialize serial communications at 115200 bps:
  Serial.begin(115200);
  //ACSR &=~(1<<ACIE);  //Turn off UART Tx
  //ACSR |=~(1<<ACD);   //Turn off UART Tx
#endif
  servo_esc.attach(PPM_SPINDLE_RPM_OUT_PIN, MIN_PPM_PULSE, MAX_PPM_PULSE);  // attaches the servo on pin PPM_SPINDLE_RPM_OUT_PIN to the servo object and sets min and max values for writes (in µs). 

}

void loop() {
  // read the analog in value:
  analogSpindleRPMValue = analogRead(ANALOG_SPINDLE_RPM_IN_PIN);
  // map it to the range of the analog out:
  ppmSpindleRPMValue = map(analogSpindleRPMValue, 0, 1023, MIN_PPM_PULSE, MAX_PPM_PULSE);
    
  //servo_esc.writeMicroseconds( (int) ppmSpindleRPMValueAvg.getAverage());  // sets the servo position according to the scaled value
  servo_esc.writeMicroseconds(ppmSpindleRPMValue);  // sets the servo position according to the scaled value


  // wait 15 milliseconds before the next loop for the analog-to-digital
  // converter to settle after the last reading and the esc/servo to geht there:
  delay(15); // waits for the servo to get there

#ifdef DEBUG_SERIAL
  // print the results to the Serial Monitor:
  //Serial.print("Spindle RPM [0..1023]= "); // Spindle RPM measured on ADC [0..1023]
  //Serial.print(analogSpindleRPMValue);
  //Serial.print("\t Servo/ESC pulse length= "); // Servo/ESC output PPM signal pulse length [MIN_PPM_PULSE µs..MAX_PPM_PULSE µs] 
  //Serial.println(ppmSpindleRPMValue);
#endif

}

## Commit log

2019-02-28 Update README.md
    added English description
2019-02-28 First commit
    First commit to Version 1.0 to Repo
2019-02-28 Delete Konzept.md
    see Readme.md
2019-03-04 V1.1
    - Version 1.1 of MPCNC Nano Estlcam Shield
    PCB schematic changes:
    # Symbol value removed (default symbol value for BOM creation)
    + Added field value "Funktion" to all symbols for part description
    # Symbol reference annotation changed
    + 12-36V power supply capability (with LM2596 Step Down Module)
2019-03-10 V1.2
    - Version 1.2 of MPCNC Nano Estlcam Shield
    PCB schematic changes:
    + Power LEDs (5mm LED) added(5V and VMot[formerly VDD])
    + 3,3V connector added
    + Output Enabled LEDs added (3 x 3mm LED + 1k resistor for OUT1,2,3), Pulls down ouput signal on startup
    # Replaced powerflag "VDD" with "VMot" (new custom symbol)
2019-03-10 Revert "V1.2"
    This reverts commit 25746ea092c74b1b8c6b498096b07c9fdffcdb93.
2019-03-10 Add Terminal block datasheet
2019-03-10 Revert "Revert "V1.2""
    This reverts commit 57979cb871c24b21395862369d7dbde15bbed53b.
2019-03-12 V1.3
    - Version 1.3 of MPCNC Nano Estlcam Shield
    PCB schematic changes:
    # Changed electrolytic capacitor values for L7805 (0,33µF + 0,1µF)
    PCB layout changes:
    # Changed footprint of electrolytic capacitor for L7805 (D=8mm/RM=3,5mm -> D=5mm/RM=2,0mm)
    # Revised heatsink footprint
2019-03-12 Minor changes for V1.3
    PCB schematic changes:
    #Changed footprints for some parts from standard lib to MPCNC lib
    PCB layout changes:
    #Added value to silk screen layer for some footprints
2019-03-15 Obsolete
2019-04-01 Public Release V1.3
2019-04-13 Resized 3D Model images
2019-04-13 Added creator name and email address
2019-04-14 Add files via upload
    Kleine Anpassung
2019-04-14 Delete Unterteil.step
    Wird durch eine andere Datei ersetzt
2019-04-14 Changes
    Ein paar kleine Anpassungen
2019-04-14 Delete Frontplatte-DSUB-Hohlbuchse.stl
    Ersatz durch neue Datei
2019-04-14 Changes
    Ein paar kleinere Updates an der Datei.
2019-04-14 Add files via upload
    DXF zum Fräsen der Frontplatte
2019-04-14 Moved to separate folder
    - separate folder for each enclosure contributor
    - minor changes in README.md
2019-04-16 V1.4
    - Version 1.4 of MPCNC Nano Estlcam Shield
    PCB schematic changes:
    # Changed LED colours (D1:red, D4:green, D5-7:Clear/red)
    PCB layout changes:
    + Footprints for LEDs added to project footprint library ("MPCNC_Shield_Footprints").
    # Changed footprint of LEDs
2019-04-18 Update
    Kleine ungenauigkeit an den Befestigungslöchern der Frontplatte korrigiert.
2019-04-18 Add files via upload
    Korrigierte Versionen
2019-04-18 Delete Frontplatte-Blanko.stl
    Wegen kleinem Fehler bzw einer Ungenauigkeit gelöscht
2019-04-18 Delete Frontplatte-komplett.stl
    Wegen kleinem Fehler bzw einer Ungenauigkeit gelöscht
2019-04-18 Delete Frontplatte-Blanko.step
    Wegen kleinem Fehler bzw einer Ungenauigkeit gelöscht
2019-04-18 Delete Frontplatte-Komplett.step
    Wegen kleinem Fehler bzw einer Ungenauigkeit gelöscht
2019-05-12 Added 3D models of MPCNC Estlcam Shield for CAD enclosure deisgn
    - added .step file
    - added .wrl file (includes pcb silkscreen)
2019-11-07 Gerber v1.4 created
2019-11-07 Housing from Henrik Word added.
    The Housing is based on Daniel's housing.
2019-11-07 Update README.md
    Translation
2019-11-11 Create Oberteil Nano Controller Box.stl
    Same as "Oberteil groß", but the is moved a bit to the middle, to have more space between fan and GX-16.
2020-04-25 Update README.md
    Hinweise Lizenz
2020-05-28 Update README.md
    Added supplier PCB/Parts (Google Forms)
2020-07-21 Firmware added for ATtiny25/45/85
    Spindle RPM-Signal to PPM-Signal conversion (e.g. for controlling RC model motor with ESCs, RC model servos, etc)
2023-04-08 Update README.md
    Removed Bestellformular-Link auf Google Forms

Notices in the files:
MPCNC Nano Estlcam Shield.kicad_pcb:
licensed under Creative Commons BY-NC-SA 4.0 license
